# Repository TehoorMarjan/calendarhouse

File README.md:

# DIY Smart Advent Calendar House 🎄

> [!WARNING]  
> This project is a work in progress. While it can serve as inspiration, it is not ready for plug-and-play use and requires additional development and customization.

<div align="center">

</div>

A fun, interactive advent calendar looking like a miniature wooden house with a drawer for each day leading up to Christmas. This project combines craftsmanship with electronics to create a delightful experience for children and grown-ups!

## Project Highlights

- **Interactive LEDs**: Each day, a specific LED lights up to guide the child to the correct drawer.
- **Drawer Detection**: Detects when a drawer is opened using Hall-effect sensors and magnets.
- **Audio Playback**: Plays music, stories, or sounds depending on opened drawer, also giving feedback when wrong drawer is opened.
- **Light Show**: Features decorative light displays synchronized with sound playback. (🚧 Planned feature)

---

## Folder Structure

- **`Fritzing`**: Contains the initial schematics created with the Fritzing software.
- **`KiCAD`**: Detailed electronic schematics and PCB designs created with KiCAD.
- **`Firmware`**: A PlatformIO project featuring the ESP32 firmware (work in progress).
- **`Documentation`**: Includes relevant datasheets and schema exports.
- **`Design`**: Includes decoration ideas, paint tests, and images of the house design.

---

## Hardware Overview

### Electronics Used
1. **ESP32-WROOM**: The main microcontroller also used for USB 5V power supply.
2. **TLC5947 Module**: 24-channel PWM driver for controlling the LEDs above each drawer, From Adafruit.
3. **2x PCF8575 IO Expanders**: To read the state of the 24 drawers via Hall-effect sensors (12 IOs each, each expander can handle up to 16 IOs).
4. **MAX98357 I2C Amplifier**: For better audio output compared to the PAM8403 module. (🚧 Realised on-board, schematics to change yet.)
5. **SPI SD Card Reader**: To store music, sound effects, or stories. Could also host update files (OTA), parameters, ...
6. **Hall-effect Sensors (A3144)**: Each drawer gets a small 10x10x1 mm *neodymium* magnet *(ferrite would be too weak)* and Hall-effect sensor to detect openings. `A3144` was selected, but requires improvement due to its active-low nature ("magnet present = on" ⇒ current is drawn almost all the time). Should select a non-latching active-high sensor instead.

---

## Tools Used

- **Fritzing**: Initial circuit layout and basic design.
- **KiCAD**: Advanced schematics and PCB design for production-ready boards.
- **PlatformIO**: Development environment for writing Arduino-based firmware for the ESP32.

---

## Getting Started

### Prerequisites
- Install [PlatformIO](https://platformio.org/) to compile and upload firmware.
- Required dependencies for the ESP32 firmware can be installed using:
  ```bash
  pio pkg install
  ```

### Hardware Assembly
1. **Electronics Integration**:
   - Connect ESP32, LEDs, sensors, and audio modules as per the schematics in the `KiCAD` folder.
   - Solder the components onto the PCB designed in `KiCAD` or use a breadboard for prototyping.

2. **House Assembly**:
   - Paint and decorate the wooden house using ideas from the `Design` folder.
   - Attach the LEDs above each drawer and install Hall-effect sensors inside.

3. **Calibration**:
   - Test the sensor detection and calibrate the thresholds for drawer opening/closing.
   - Load the firmware onto the ESP32 to test the LED control and audio playback.

## Future Enhancements

- Add Wi-Fi capabilities for remote control (🚧 ongoing).
- Integrate a mobile/web app.
- Explore active-high Hall-effect sensors for smoother drawer state detection.

## License

Feel free to reuse components of this project, **subject to their respective licenses**. Please note that third-party components (such as Fritzing and KiCAD parts) may have their own licensing terms, which you should review accordingly. (⚠️ TODO: Check the licenses for each part).

### My Original Work:

Released under [CC0 1.0 Universal (Public Domain Dedication)](https://creativecommons.org/publicdomain/zero/1.0/). This means you can use *my* artwork and *my* code for any purpose without any restrictions.

In short, you are free to use, modify, and distribute both the code and artwork with very few limitations.

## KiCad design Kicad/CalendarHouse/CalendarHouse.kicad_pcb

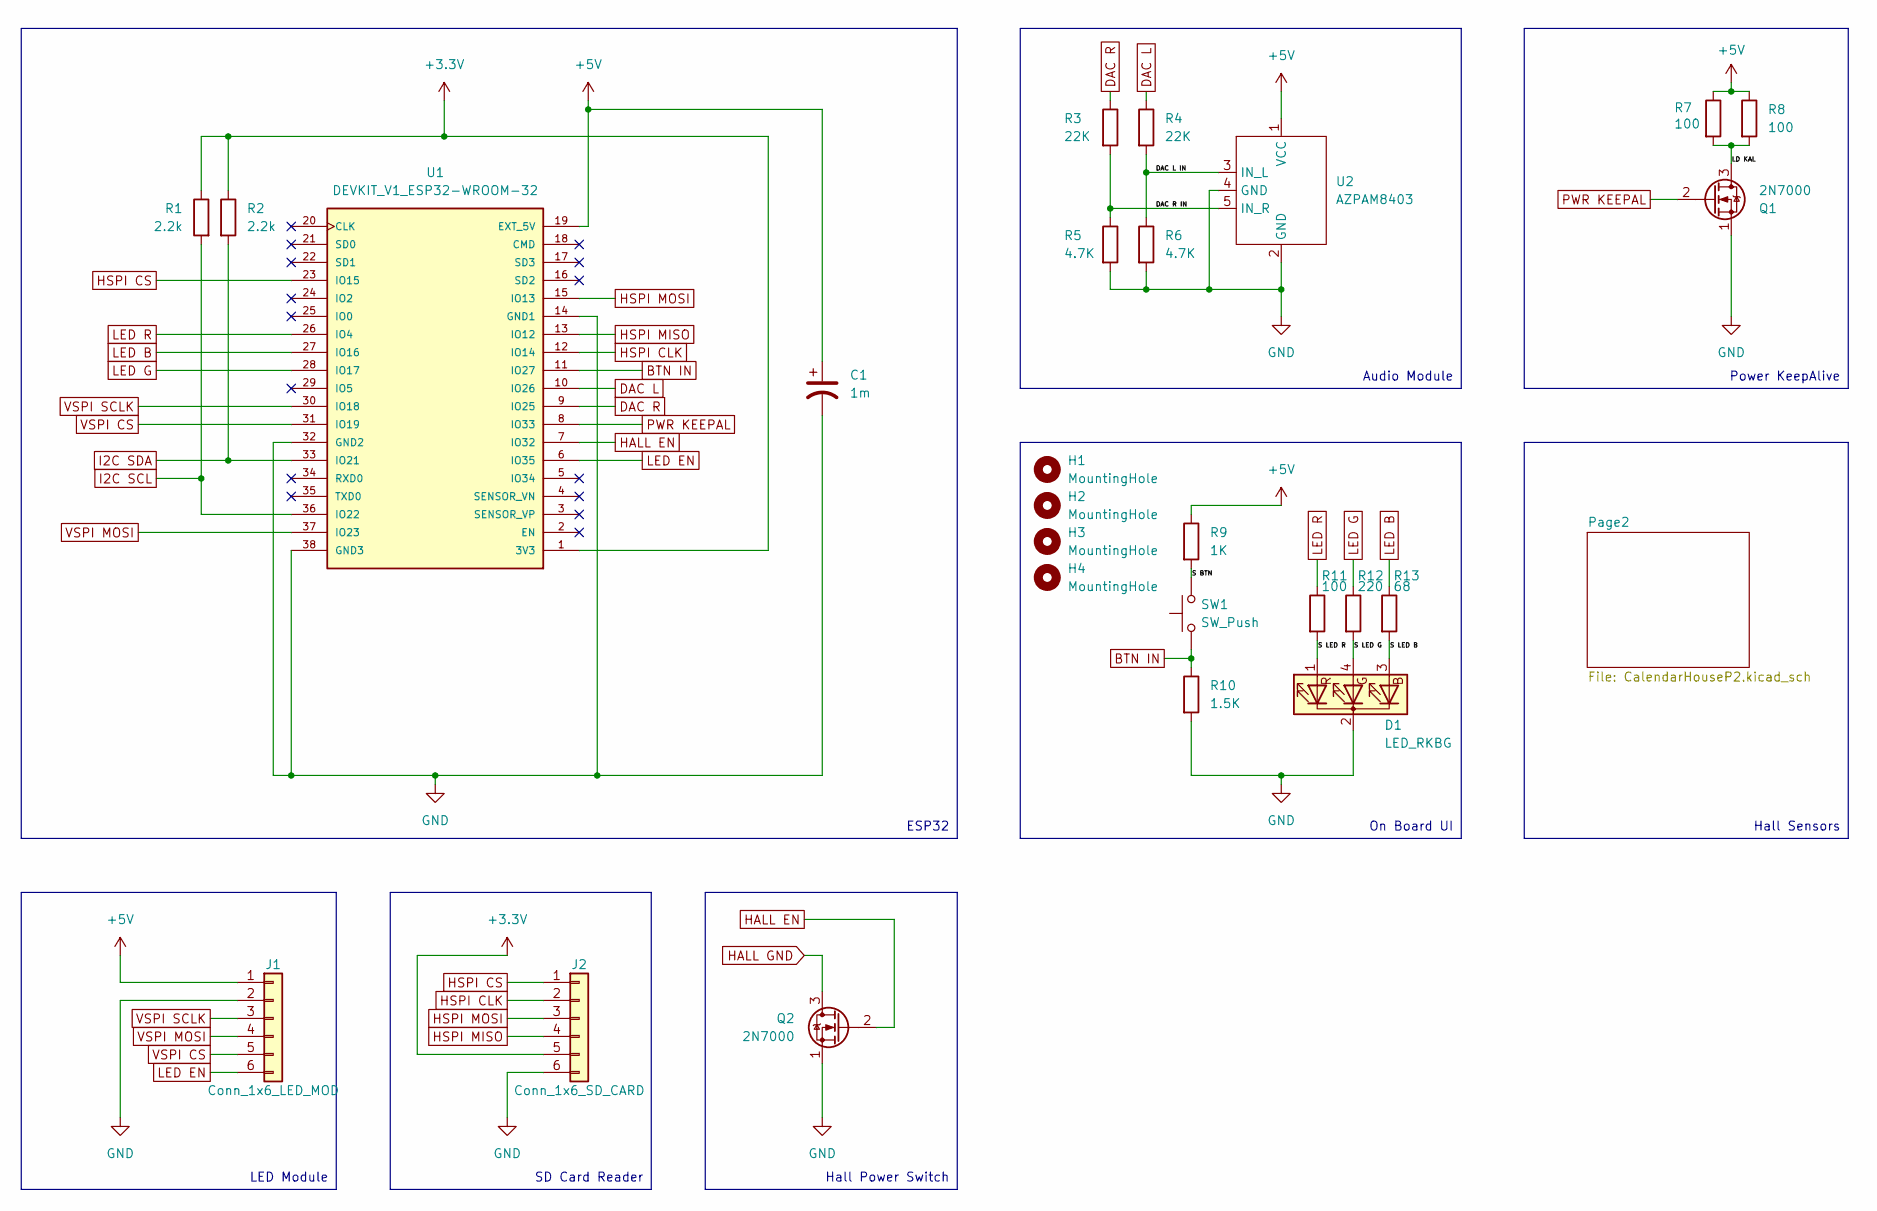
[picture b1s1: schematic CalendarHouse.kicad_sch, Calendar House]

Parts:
C1: 1m; C_Radial_D10.0mm_H12.5mm_P5.00mm
D1: LED_RKBG; LED_D5.0mm-4_RGB
H1, H2, H3, H4: MountingHole; MountingHole_2.2mm_M2_DIN965
J1: Conn_1x6_LED_MOD; PinHeader_1x06_P2.54mm_Vertical
J2: Conn_1x6_SD_CARD; PinHeader_1x06_P2.54mm_Vertical
Q1, Q2: 2N7000; TO-92_Inline
R1, R2: 2.2k; R_0805_2012Metric_Pad1.20x1.40mm_HandSolder
R3, R4: 22K; R_0805_2012Metric_Pad1.20x1.40mm_HandSolder
R5, R6: 4.7K; R_0805_2012Metric_Pad1.20x1.40mm_HandSolder
R7, R8: 100; R_1206_3216Metric_Pad1.30x1.75mm_HandSolder
R9: 1K; R_0805_2012Metric_Pad1.20x1.40mm_HandSolder
R10: 1.5K; R_0805_2012Metric_Pad1.20x1.40mm_HandSolder
R11: 100; R_0805_2012Metric_Pad1.20x1.40mm_HandSolder
R12: 220; R_0805_2012Metric_Pad1.20x1.40mm_HandSolder
R13: 68; R_0805_2012Metric_Pad1.20x1.40mm_HandSolder
SW1: SW_Push; SW_PUSH-12mm; MPN TL1100D
U1: DEVKIT_V1_ESP32-WROOM-32; MODULE_DEVKIT_V1_ESP32-WROOM-32; PARTREV N/A
U2: AZPAM8403; Mini PAM8403 Module OnlyInput

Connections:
+3.3V: J2.5, R1.1, R2.1, U1.1 (3V3)
+5V: C1.1, J1.1, R7.1, R8.1, R9.1, U1.19 (EXT_5V), U2.1 (VCC); also elsewhere on the board
/DAC L IN: R4.2, R6.1, U2.3 (IN_L)
/DAC R IN: R3.2, R5.1, U2.5 (IN_R)
/LD KAL: Q1.3 (D), R7.2, R8.2
/S BTN: R9.2, SW1.2
/S LED B: D1.3 (BA), R13.2
/S LED G: D1.4 (GA), R12.2
/S LED R: D1.1 (RA), R11.2
BTN IN: R10.1, SW1.1, U1.11 (IO27)
DAC L: R4.1, U1.10 (IO26)
DAC R: R3.1, U1.9 (IO25)
GND: C1.2, D1.2 (K), J1.2, J2.6, Q1.1 (S), Q2.1 (S), R5.2, R6.2, R10.2, U1.14 (GND1), U1.32 (GND2), U1.38 (GND3), U2.2 (GND), U2.4 (GND)
HALL EN: Q2.2 (G), U1.7 (IO32)
HALL GND: Q2.3 (D); also elsewhere on the board
HSPI CLK: J2.2, U1.12 (IO14)
HSPI CS: J2.1, U1.23 (IO15)
HSPI MISO: J2.4, U1.13 (IO12)
HSPI MOSI: J2.3, U1.15 (IO13)
I2C SCL: R1.2, U1.36 (IO22); also elsewhere on the board
I2C SDA: R2.2, U1.33 (IO21); also elsewhere on the board
LED B: R13.1, U1.27 (IO16)
LED EN: J1.6, U1.6 (IO35)
LED G: R12.1, U1.28 (IO17)
LED R: R11.1, U1.26 (IO4)
PWR KEEPAL: Q1.2 (G), U1.8 (IO33)
VSPI CS: J1.5, U1.31 (IO19)
VSPI MOSI: J1.4, U1.37 (IO23)
VSPI SCLK: J1.3, U1.30 (IO18)

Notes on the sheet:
Power KeepAlive
Audio Module
LED Module
ESP32
Hall Sensors
Hall Power Switch
On Board UI
SD Card Reader

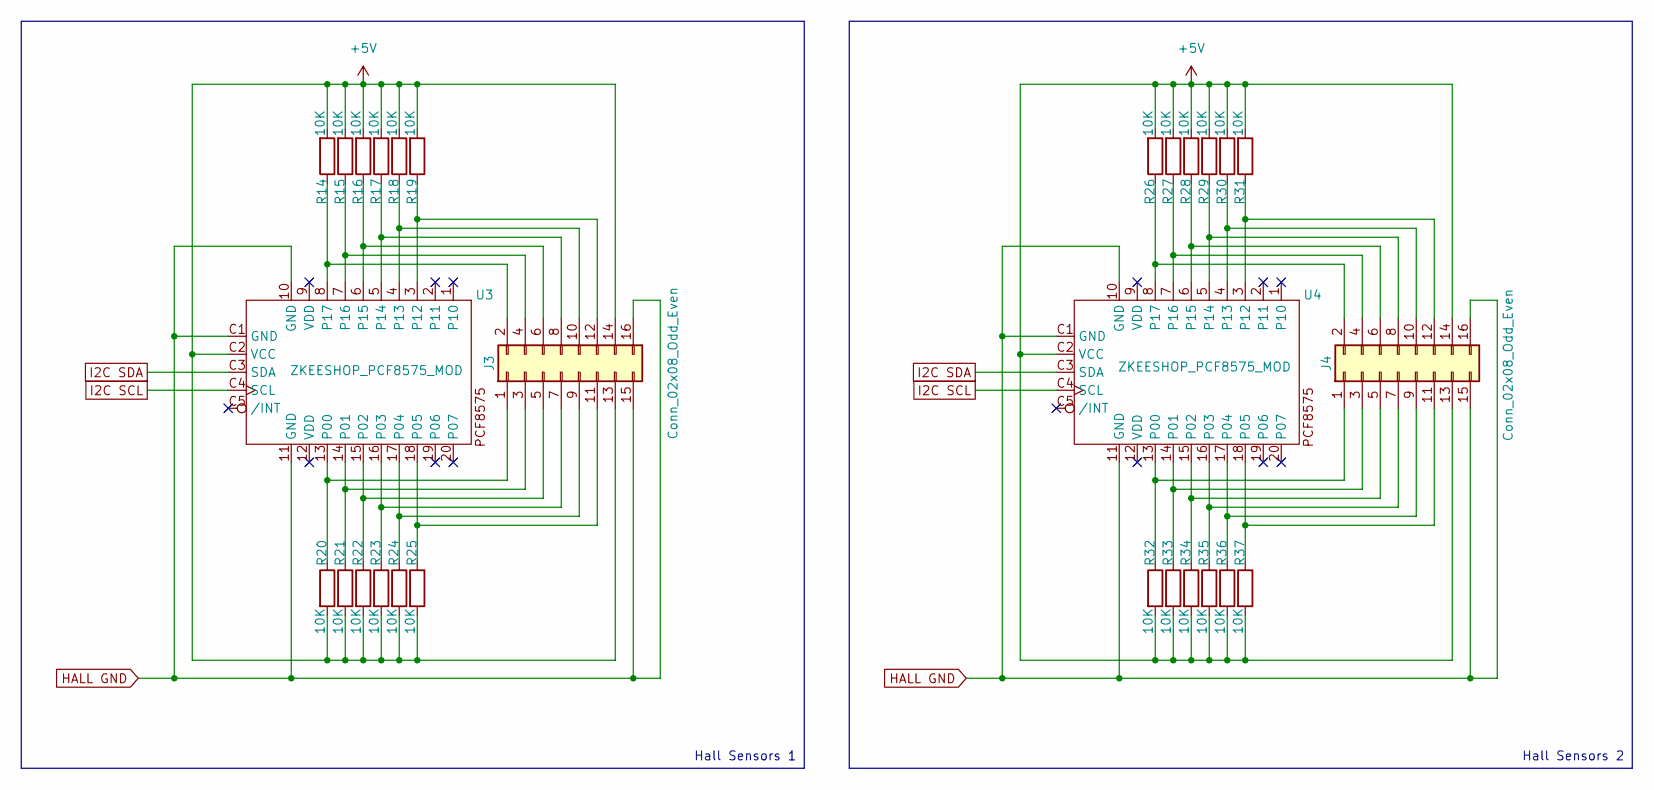
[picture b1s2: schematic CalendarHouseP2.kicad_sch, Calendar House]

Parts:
J3, J4: Conn_02x08_Odd_Even; PinHeader_2x08_P2.54mm_Vertical
R14, R15, R16, R17, R18, R20, R21, R22, R23, R24, R26, R27, R28, R29, R30, R32, R33, R34, R35, R36: 10K; R_0805_2012Metric_Pad1.20x1.40mm_HandSolder
R19, R25, R31, R37: 10K; R_1206_3216Metric_Pad1.30x1.75mm_HandSolder
U3, U4: ZKEESHOP_PCF8575_MOD; 16-bit IO Expander

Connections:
+5V: J3.13, J3.14, J4.13, J4.14, R14.2, R15.2, R16.2, R17.2, R18.2, R19.2, R20.2, R21.2, R22.2, R23.2, R24.2, R25.2, R26.2, R27.2, R28.2, R29.2, R30.2, R31.2, R32.2, R33.2, R34.2, R35.2, R36.2, R37.2, U3.C2 (VCC), U4.C2 (VCC); also elsewhere on the board
HALL GND: J3.15, J3.16, J4.15, J4.16, U3.10 (GND), U3.11 (GND), U3.C1 (GND), U4.10 (GND), U4.11 (GND), U4.C1 (GND); also elsewhere on the board
I2C SCL: U3.C4 (SCL), U4.C4 (SCL); also elsewhere on the board
I2C SDA: U3.C3 (SDA), U4.C3 (SDA); also elsewhere on the board
unnamed: J3.1, R20.1, U3.13 (P00)
unnamed: J3.2, R14.1, U3.8 (P17)
unnamed: J3.3, R21.1, U3.14 (P01)
unnamed: J3.4, R15.1, U3.7 (P16)
unnamed: J3.5, R22.1, U3.15 (P02)
unnamed: J3.6, R16.1, U3.6 (P15)
unnamed: J3.7, R23.1, U3.16 (P03)
unnamed: J3.8, R17.1, U3.5 (P14)
unnamed: J3.9, R24.1, U3.17 (P04)
unnamed: J3.10, R18.1, U3.4 (P13)
unnamed: J3.11, R25.1, U3.18 (P05)
unnamed: J3.12, R19.1, U3.3 (P12)
unnamed: J4.1, R32.1, U4.13 (P00)
unnamed: J4.2, R26.1, U4.8 (P17)
unnamed: J4.3, R33.1, U4.14 (P01)
unnamed: J4.4, R27.1, U4.7 (P16)
unnamed: J4.5, R34.1, U4.15 (P02)
unnamed: J4.6, R28.1, U4.6 (P15)
unnamed: J4.7, R35.1, U4.16 (P03)
unnamed: J4.8, R29.1, U4.5 (P14)
unnamed: J4.9, R36.1, U4.17 (P04)
unnamed: J4.10, R30.1, U4.4 (P13)
unnamed: J4.11, R37.1, U4.18 (P05)
unnamed: J4.12, R31.1, U4.3 (P12)

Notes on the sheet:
Hall Sensors 1
Hall Sensors 2

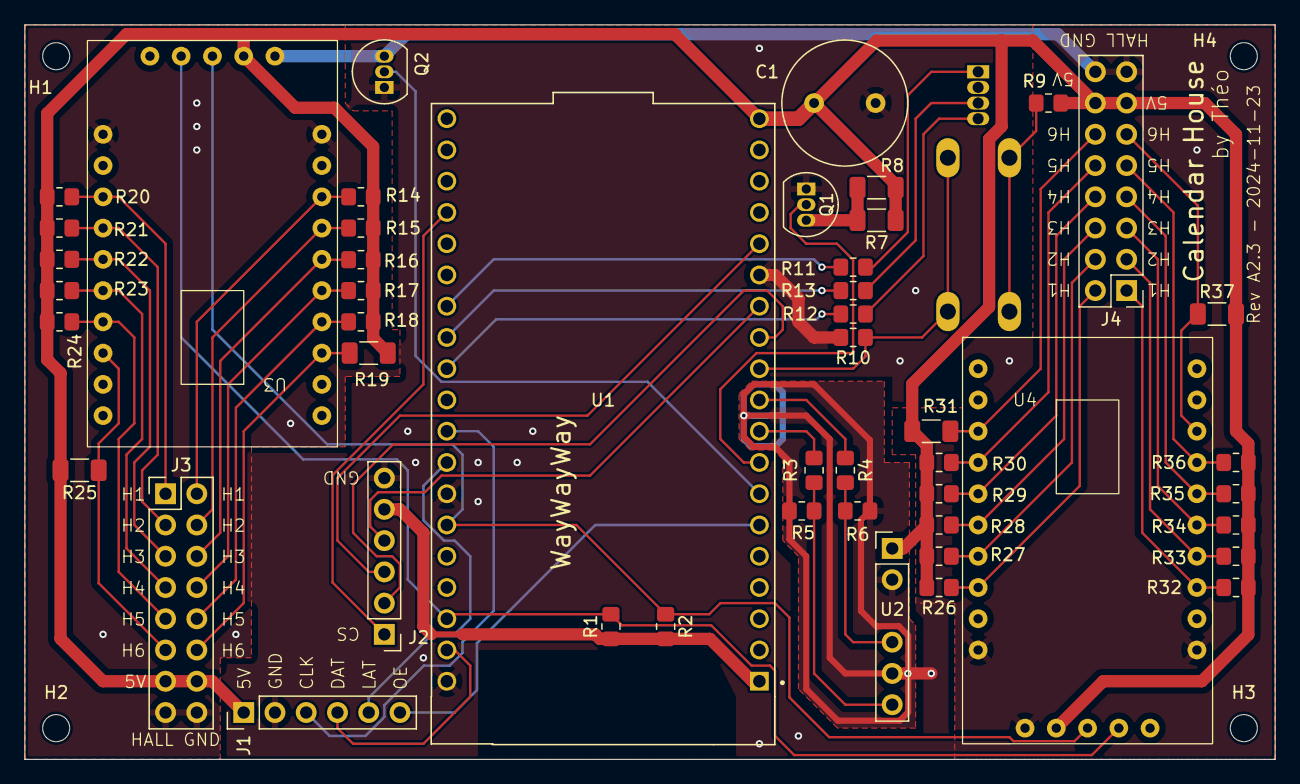
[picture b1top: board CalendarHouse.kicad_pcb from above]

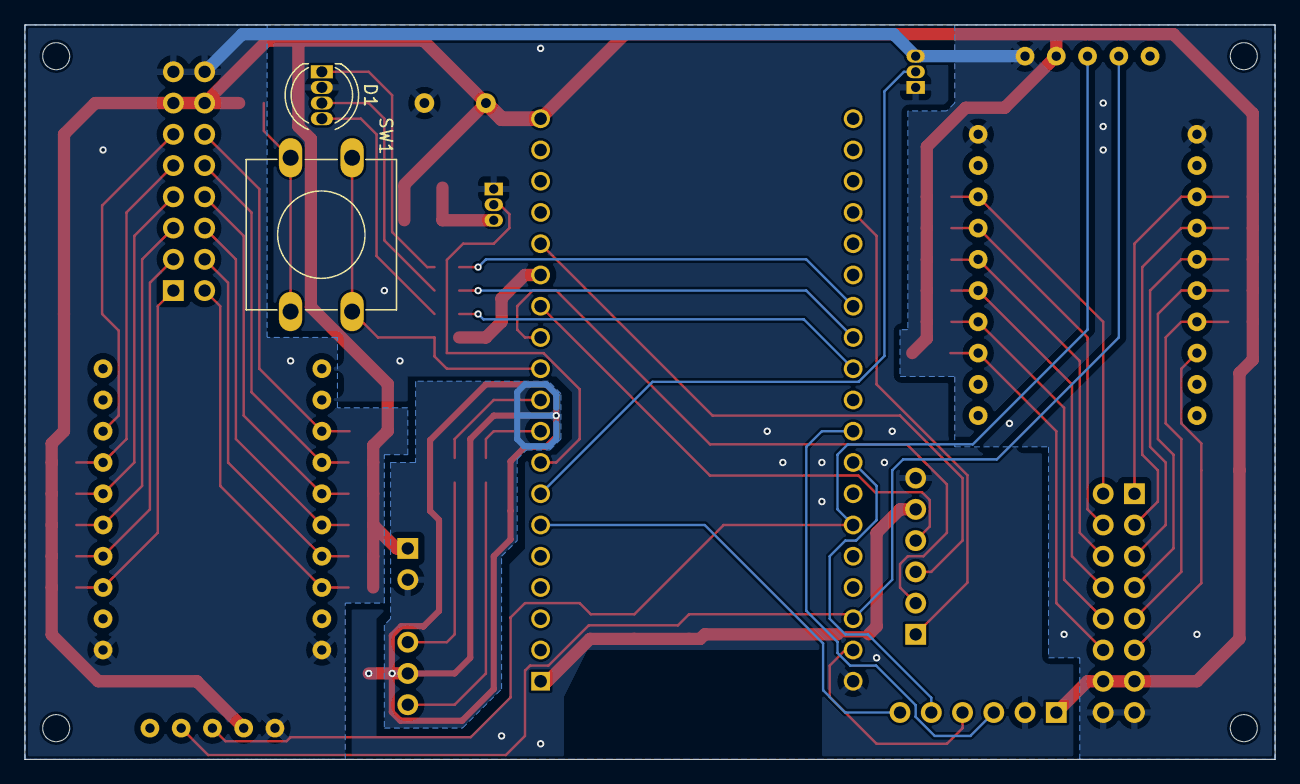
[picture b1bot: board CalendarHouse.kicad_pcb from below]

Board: 2 copper layers, 101.6 x 59.7 mm, 54 parts (2 on the bottom side), 53 nets.

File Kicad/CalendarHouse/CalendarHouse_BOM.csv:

"Reference","Value","Datasheet","Footprint","Qty","DNP","Availability"
"C1","1m","~","Capacitor_THT:C_Radial_D10.0mm_H12.5mm_P5.00mm","1","","In Stock"
"D1","LED_RKBG","https://www.farnell.com/datasheets/3497864.pdf","LED_THT:LED_D5.0mm-4_RGB","1","","In Stock"
"J1","Conn_1x6_LED_MOD","~","Connector_PinHeader_2.54mm:PinHeader_1x06_P2.54mm_Vertical","1","","Ordered"
"J2","Conn_1x6_SD_CARD","~","Connector_PinHeader_2.54mm:PinHeader_1x06_P2.54mm_Vertical","1","","Ordered"
"J3,J4","Conn_02x08_Odd_Even","~","Connector_PinHeader_2.54mm:PinHeader_2x08_P2.54mm_Vertical","2","","Ordered"
"Q1,Q2","2N7000","https://www.vishay.com/docs/70226/70226.pdf","Package_TO_SOT_THT:TO-92_Inline","2","","In Stock"
"R1,R2","2.2k","~","Resistor_SMD:R_0805_2012Metric_Pad1.20x1.40mm_HandSolder","2","","Ordered"
"R3,R4","22K","~","Resistor_SMD:R_0805_2012Metric_Pad1.20x1.40mm_HandSolder","2","","Ordered"
"R5,R6","4.7K","~","Resistor_SMD:R_0805_2012Metric_Pad1.20x1.40mm_HandSolder","2","","Ordered"
"R7,R8","100","~","Resistor_SMD:R_1206_3216Metric_Pad1.30x1.75mm_HandSolder","2","","Ordered"
"R9","1K","~","Resistor_SMD:R_0805_2012Metric_Pad1.20x1.40mm_HandSolder","1","","Ordered"
"R10","1.5K","~","Resistor_SMD:R_0805_2012Metric_Pad1.20x1.40mm_HandSolder","1","","Ordered"
"R11","100","~","Resistor_SMD:R_0805_2012Metric_Pad1.20x1.40mm_HandSolder","1","","Ordered"
"R12","220","~","Resistor_SMD:R_0805_2012Metric_Pad1.20x1.40mm_HandSolder","1","","Ordered"
"R13","68","~","Resistor_SMD:R_0805_2012Metric_Pad1.20x1.40mm_HandSolder","1","","Ordered"
"R14,R15,R16,R17,R18,R20,R21,R22,R23,R24,R26,R27,R28,R29,R30,R32,R33,R34,R35,R36","10K","~","Resistor_SMD:R_0805_2012Metric_Pad1.20x1.40mm_HandSolder","20","","Ordered"
"R19,R25,R31,R37","10K","~","Resistor_SMD:R_1206_3216Metric_Pad1.30x1.75mm_HandSolder","4","","Ordered"
"SW1","SW_Push","https://sten-eswitch-13110800-production.s3.amazonaws.com/sy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","Button_Switch_THT:SW_PUSH-12mm","1","","In Stock"
"U1","DEVKIT_V1_ESP32-WROOM-32","https://www.espressif.com/sites/default/files/documentation/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","Kicad:MODULE_DEVKIT_V1_ESP32-WROOM-32","1","","In Stock"
"U2","AZPAM8403","https://cdn.shopify.com/s/files/1/1509/1638/files/Mini-PAM84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","Kicad:Mini PAM8403 Module OnlyInput","1","","In Stock"
"U3,U4","ZKEESHOP_PCF8575_MOD","https://www.tinytronics.nl/shop/index.php?route=product/prod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","Kicad:16-bit IO Expander","2","","In Stock"

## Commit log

2024-11-25 First Commit
    - Archived Fritzing project, replaced by Kicad
    - Kicad project sent to production at PCBWay
    - Includes color research of houses
2024-11-25 PlatformIO Init and SD Card
    - Init PlatformIO for Firmware
    - Had to burn eFuses due to GPIO12 missuse
    - Proof Of Concept for SD Card Reader
2024-11-26 PoC LED PWM
    - Using Adafruit lib bitbanger
    - Cleaned SD Card
    - GPIO35 is not suitable for LED_EN
2024-11-27 LED Driver
    - Own LED driver
2024-11-27 Add Audio Controller
    - Audio Task
    - Currently, poor sound output
    - Should move to own task
2024-11-27 Add extra buffering to Audio
    - Still sounds awful...
2024-12-01 Update Schematics due to missing resistor value
    - Corrected Design
    - New resistors for button due to 1.5k missing in my set
2024-12-01 Added Mono Audio
    - Using ESP32-audioI2S
    - MAX98357a
    - Works great
2024-12-01 Add network control
    - WifiManager
    - Hostname
2024-12-01 Leds
    - Doesn't work yet
2024-12-13 Add README
    and two images.
